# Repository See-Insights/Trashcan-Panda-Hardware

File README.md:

# Trashcan-Panda-Hardware
 Trashcan Panda project hardware files

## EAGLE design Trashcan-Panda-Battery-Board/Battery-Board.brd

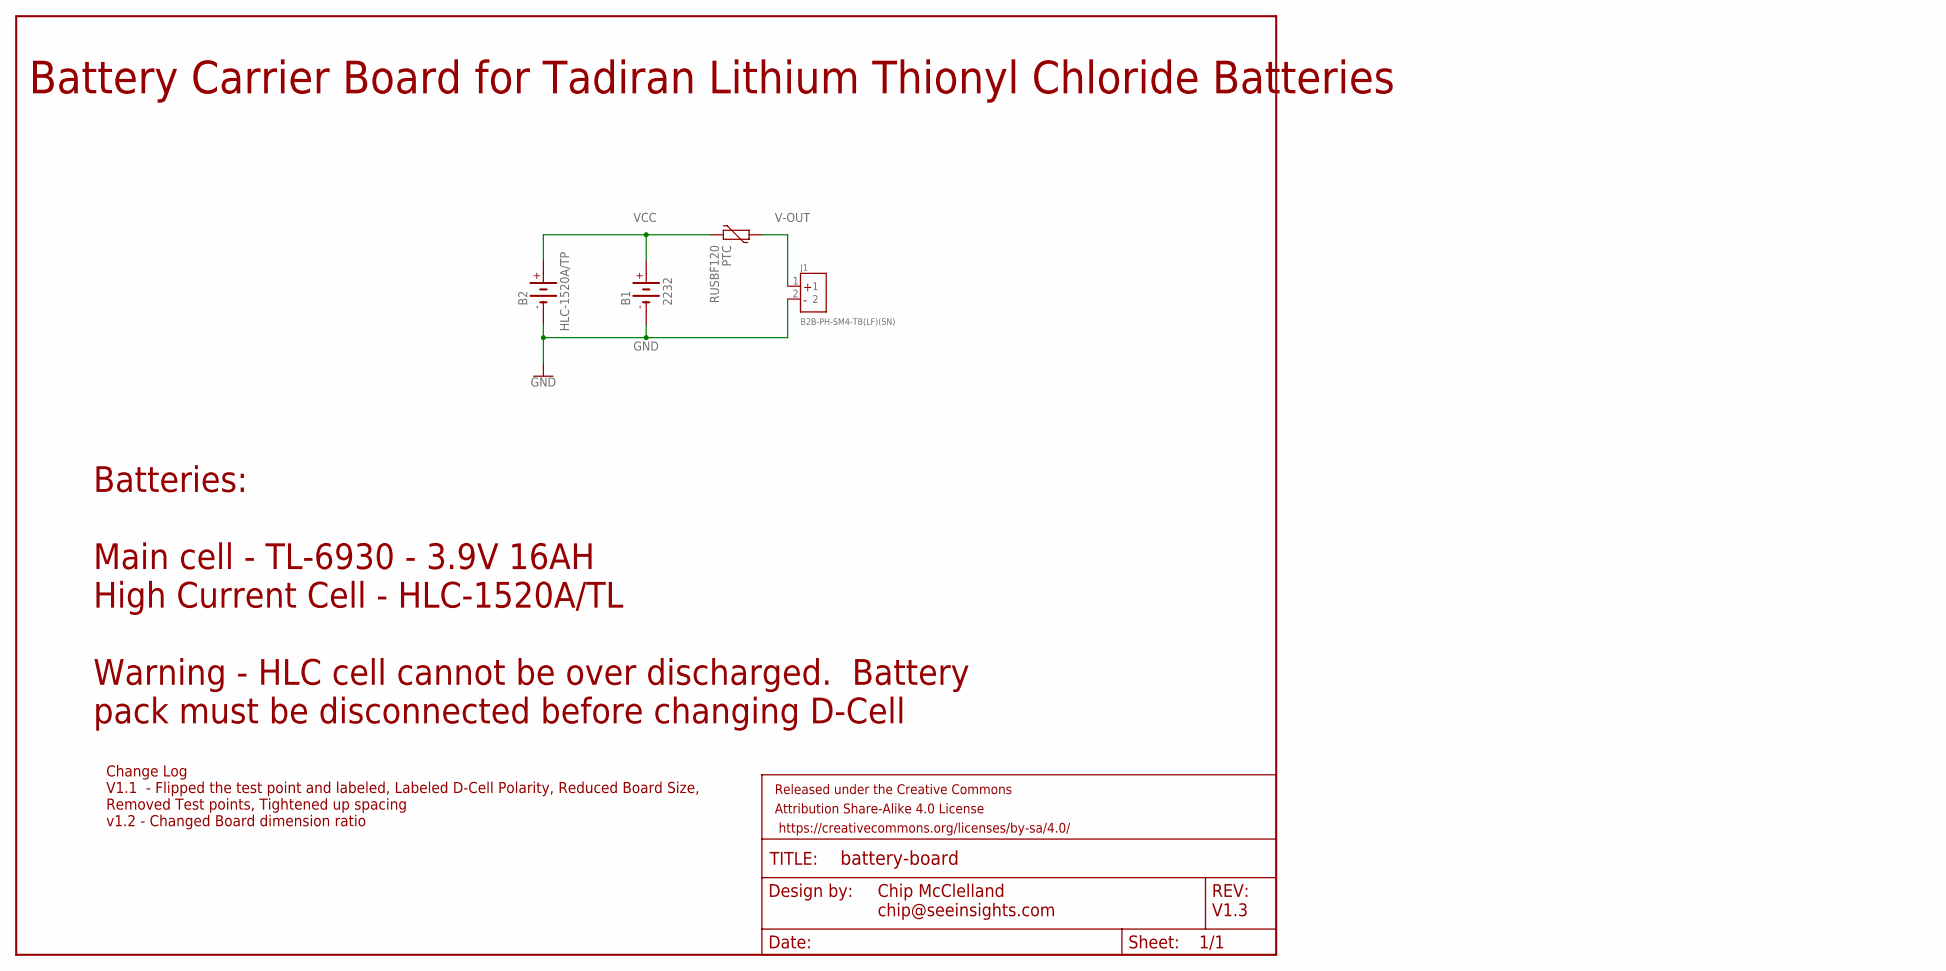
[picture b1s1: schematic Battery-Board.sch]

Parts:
B1: 2232
B2: HLC-1520A/TP
FRAME1: FRAME-LETTER; CREATIVE_COMMONS
J1: B2B-PH-SM4-TB(LF)(SN); JST_B2B-PH-SM4-TB(LF)(SN)
PTC: RUSBF120; PTC-RUSBF120

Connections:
GND: B1.-, B2.-, B2.-- (-), J1.2
V-OUT: J1.1, PTC.2
VCC: B1.+, B2.+, PTC.1

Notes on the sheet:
Battery Carrier Board for Tadiran Lithium Thionyl Chloride Batteries
Batteries: Main cell - TL-6930 - 3.9V 16AH High Current Cell - HLC-1520A/TL Warning - HLC cell cannot be over discharged. Battery pack must be disconnected before changing D-Cell
Chip McClelland chip@seeinsights.com
V1.3
Change Log V1.1 - Flipped the test point and labeled, Labeled D-Cell Polarity, Reduced Board Size, Removed Test points, Tightened up spacing v1.2 - Changed Board dimension ratio

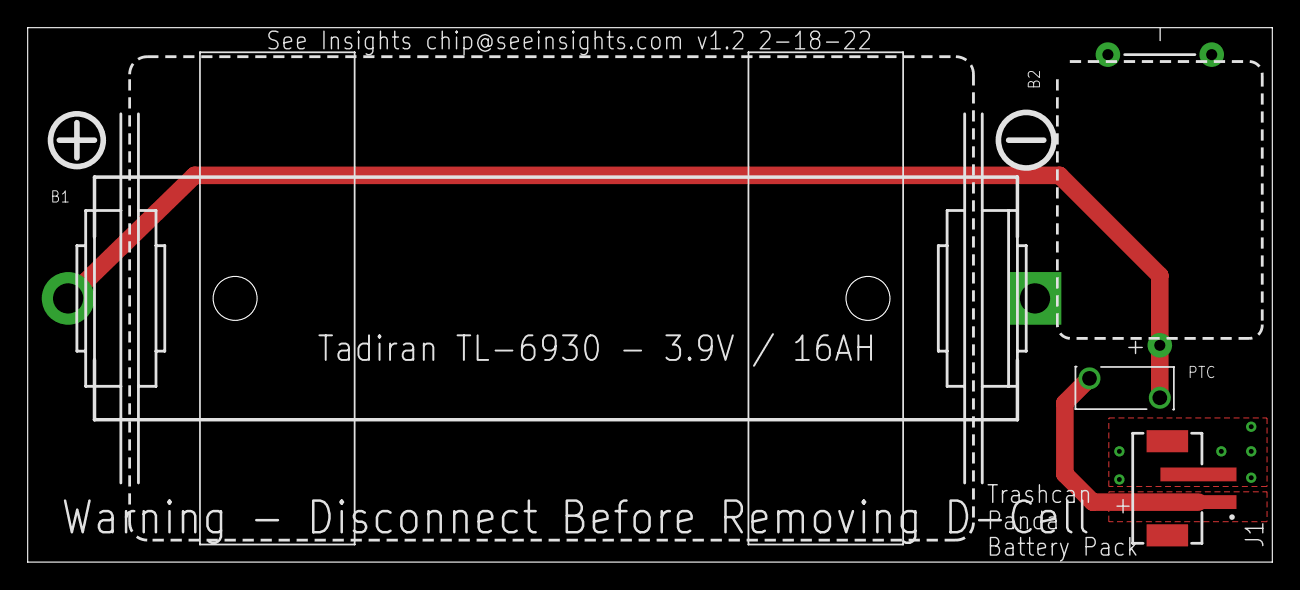
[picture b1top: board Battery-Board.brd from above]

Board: 2 copper layers, 89.9 x 38.6 mm, 5 parts (0 on the bottom side), 3 nets.

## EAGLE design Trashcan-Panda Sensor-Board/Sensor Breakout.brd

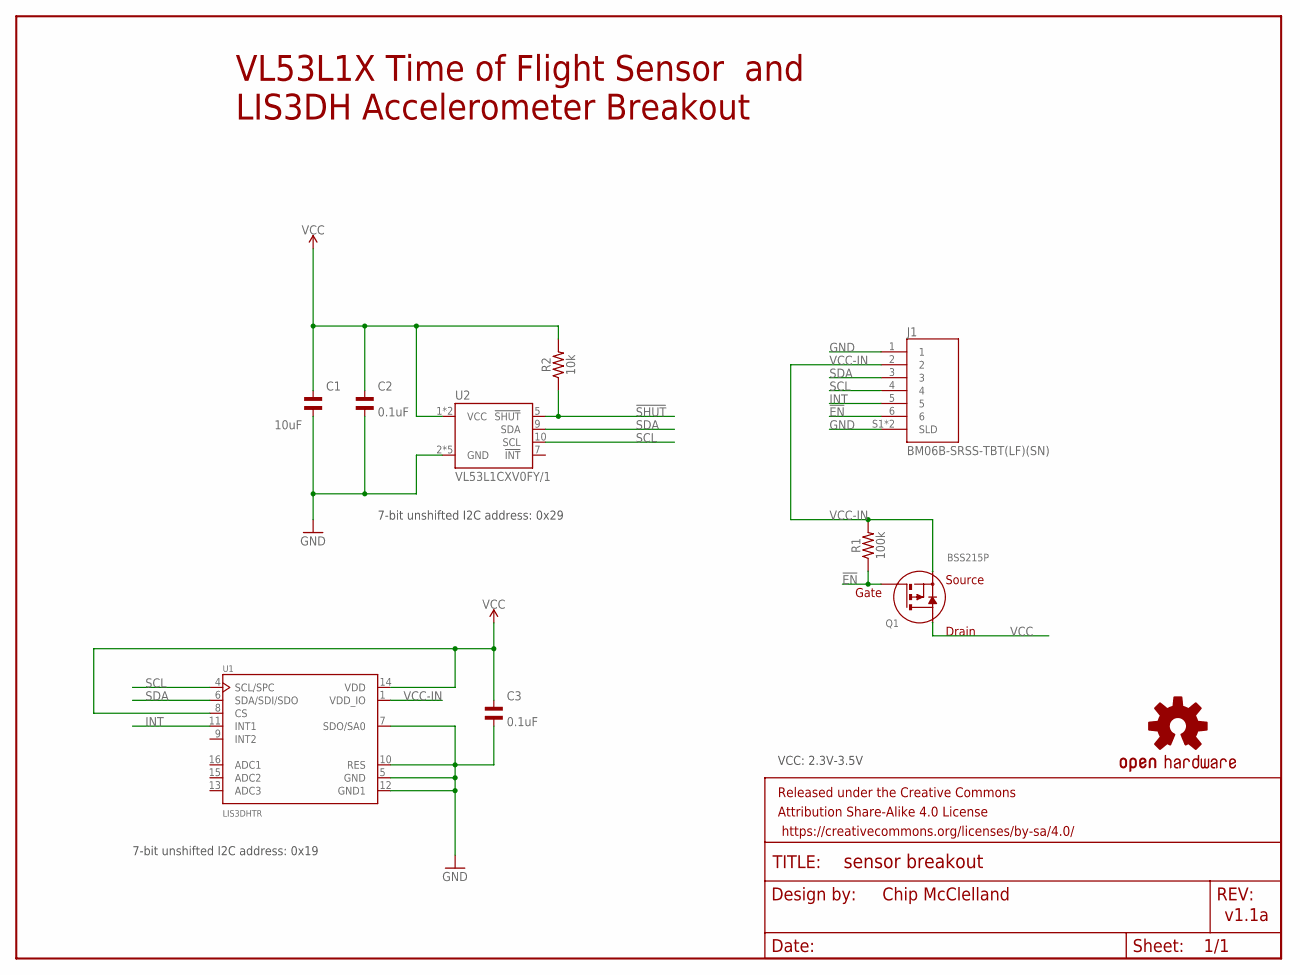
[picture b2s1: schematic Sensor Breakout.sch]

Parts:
C1: 10uF; C1206
C2, C3: 0.1uF; C0805
FRAME1: FRAME-LETTER; CREATIVE_COMMONS
J1: BM06B-SRSS-TBT(LF)(SN); JST_BM06B-SRSS-TB(LF)(SN)
LOGO1: OSHW-LOGOMINI; OSHW-LOGO-MINI
Q1: BSS215P; SOT-23_3L_ONS-M
R1: 100k; 0805; MPN MF-RES-0805-100K
R2: 10k; 0805
U1: LIS3DHTR; PQFN50P300X300X100-16N
U2: VL53L1CXV0FY/1; VL53L1X

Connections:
!EN: J1.6, Q1.1 (GATE), R1.1
!SHUT: R2.1, U2.5 (!SHUT)
GND: C1.P$2, C2.P$2, C3.P$2, J1.1, J1.S1 (SLD), J1.S2 (SLD), U1.5 (GND), U1.7 (SDO/SA0), U1.10 (RES), U1.12 (GND1), U2.2 (GND), U2.3 (GND), U2.4 (GND), U2.6 (GND), U2.12 (GND)
INT: J1.5, U1.11 (INT1)
SCL: J1.4, U1.4 (SCL/SPC), U2.10 (SCL)
SDA: J1.3, U1.6 (SDA/SDI/SDO), U2.9 (SDA)
VCC: C1.P$1, C2.P$1, C3.P$1, Q1.3 (DRAIN), R2.2, U1.8 (CS), U1.14 (VDD), U2.1 (VCC), U2.11 (VCC)
VCC-IN: J1.2, Q1.2 (SOURCE), R1.2, U1.1 (VDD_IO)

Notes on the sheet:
Chip McClelland
v1.1a
7-bit unshifted I2C address: 0x29
VCC: 2.3V-3.5V
VL53L1X Time of Flight Sensor and LIS3DH Accelerometer Breakout
7-bit unshifted I2C address: 0x19

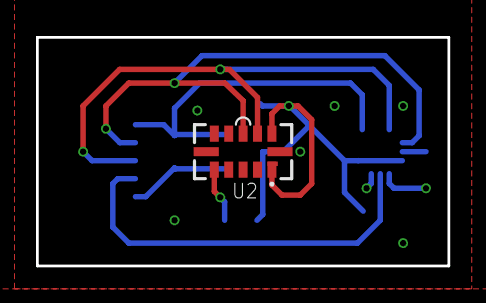
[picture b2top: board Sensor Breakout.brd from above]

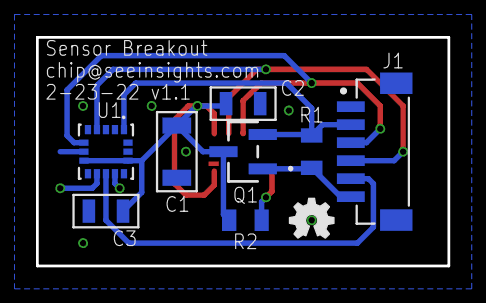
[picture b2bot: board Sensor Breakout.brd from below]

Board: 2 copper layers, 22.9 x 12.7 mm, 11 parts (9 on the bottom side), 8 nets.

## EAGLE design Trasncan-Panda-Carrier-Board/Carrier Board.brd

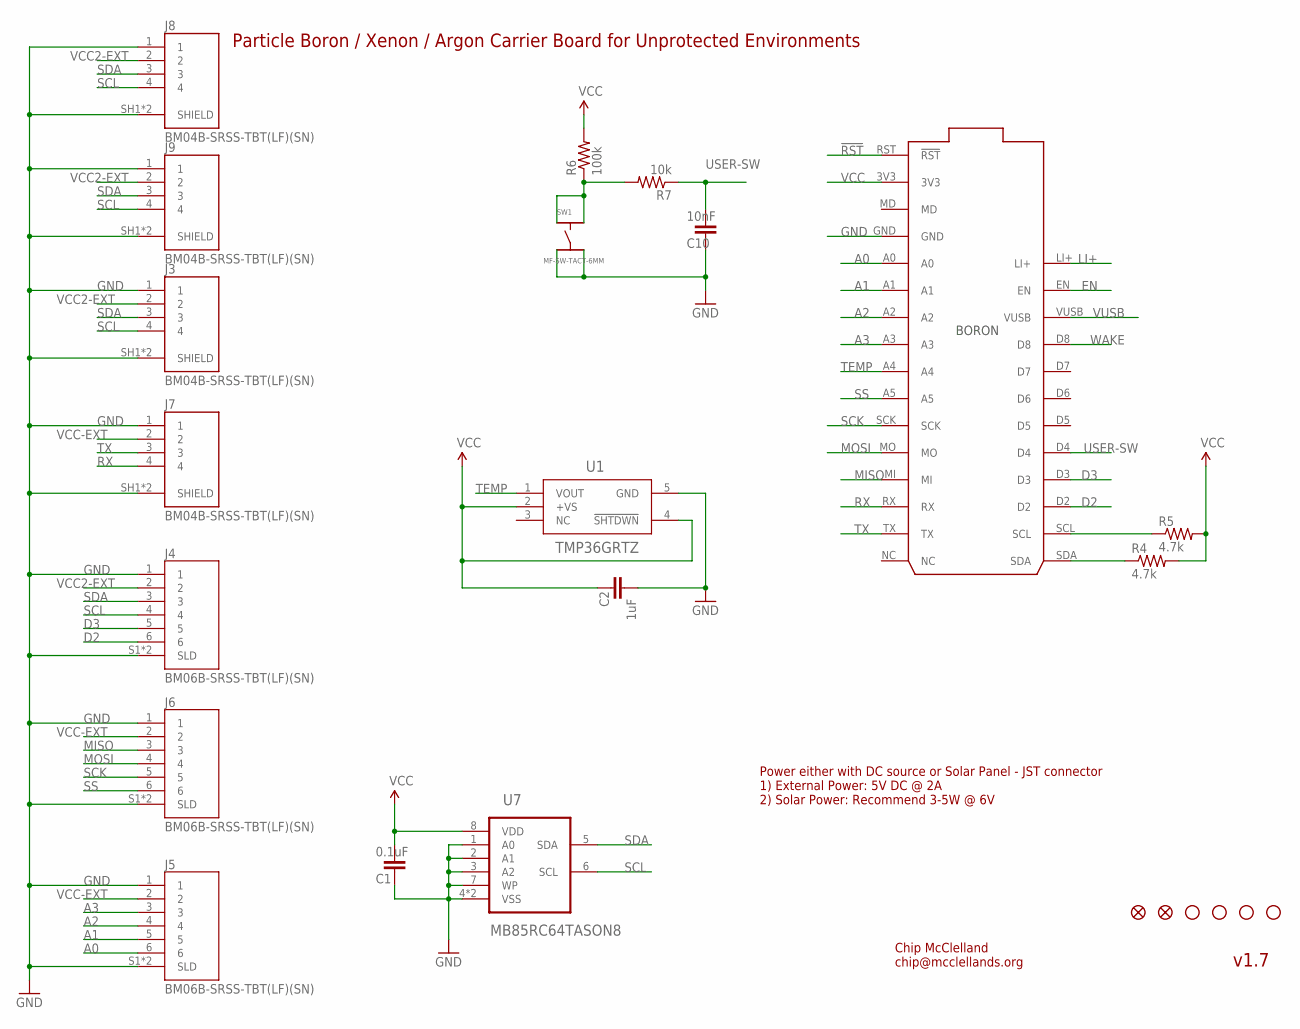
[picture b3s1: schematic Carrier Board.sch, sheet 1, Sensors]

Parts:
C1: 0.1uF; 0805@1; MPN MF-CAP-0805-0.1uF
C2: 1uF; 0805@1; MPN MF-CAP-0805-1uF
C10: 10nF; 0805@1; MPN 08051C103K4T2A
FD1, FD2: FIDUCIALUFIDUCIAL; FIDUCIAL-MICRO
J3, J7, J8, J9: BM04B-SRSS-TBT(LF)(SN); CONN_BM04B-SRSS-TBT(LF)(SN)
J4, J5, J6: BM06B-SRSS-TBT(LF)(SN); JST_BM06B-SRSS-TB(LF)(SN)
JP3, JP4, JP5, JP6: STAND-OFF
P1: Particle Boron / Xenon / Argon; PARTICLE-DEVICES_BORON
R4, R5: 4.7k; 0805; MPN MF-RES-0805-4.7K
R6: 100k; 0805; MPN MF-RES-0805-100K
R7: 10k; 0805; MPN MF-RES-0805-10K
SW1: MF-SW-TACT-6MM; TACT6MM
U1: TMP36GRTZ; RJ_5_ADI; MANUFACTURER_PART_NUMBER TMP36GRTZ-REEL7
U7: MB85RC64TASON8; SON50P200X300X75-9N

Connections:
!RST: P1.RST (!RST); also elsewhere on the board
A0: J5.6, P1.A0
A1: J5.5, P1.A1
A2: J5.4, P1.A2
A3: J5.3, P1.A3
D2: J4.6, P1.D2; also elsewhere on the board
D3: J4.5, P1.D3; also elsewhere on the board
EN: P1.EN; also elsewhere on the board
GND: C1.2, C2.2, C10.2, J3.1, J3.SH1 (SHIELD), J3.SH2 (SHIELD), J4.1, J4.S1 (SLD), J4.S2 (SLD), J5.1, J5.S1 (SLD), J5.S2 (SLD), J6.1, J6.S1 (SLD), J6.S2 (SLD), J7.1, J7.SH1 (SHIELD), J7.SH2 (SHIELD), J8.1, J8.SH1 (SHIELD), J8.SH2 (SHIELD), J9.1, J9.SH1 (SHIELD), J9.SH2 (SHIELD), P1.GND, SW1.P$3, SW1.P$4, U1.5 (GND), U7.1 (A0), U7.2 (A1), U7.3 (A2), U7.4 (VSS), U7.7 (WP), U7.9 (VSS); also elsewhere on the board
LI+: P1.LI+; also elsewhere on the board
MISO: J6.3, P1.MI
MOSI: J6.4, P1.MO
unnamed: R6.1, R7.2, SW1.P$1, SW1.P$2
RX: J7.4, P1.RX
SCK: J6.5, P1.SCK
SCL: J3.4, J4.4, J8.4, J9.4, P1.SCL, R5.1, U7.6 (SCL); also elsewhere on the board
SDA: J3.3, J4.3, J8.3, J9.3, P1.SDA, R4.1, U7.5 (SDA); also elsewhere on the board
SS: J6.6, P1.A5
TEMP: P1.A4, U1.1 (VOUT)
TX: J7.3, P1.TX
USER-SW: C10.1, P1.D4, R7.1
VCC: C1.1, C2.1, P1.3V3, R4.2, R5.2, R6.2, U1.2 (+VS), U1.4 (!SHTDWN), U7.8 (VDD); also elsewhere on the board
VCC2-EXT: J3.2, J4.2, J8.2, J9.2; also elsewhere on the board
VCC-EXT: J5.2, J6.2, J7.2; also elsewhere on the board
VUSB: P1.VUSB; also elsewhere on the board
WAKE: P1.D8; also elsewhere on the board

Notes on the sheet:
Chip McClelland chip@mcclellands.org
v1.7
Power either with DC source or Solar Panel - JST connector 1) External Power: 5V DC @ 2A 2) Solar Power: Recommend 3-5W @ 6V
Particle Boron / Xenon / Argon Carrier Board for Unprotected Environments

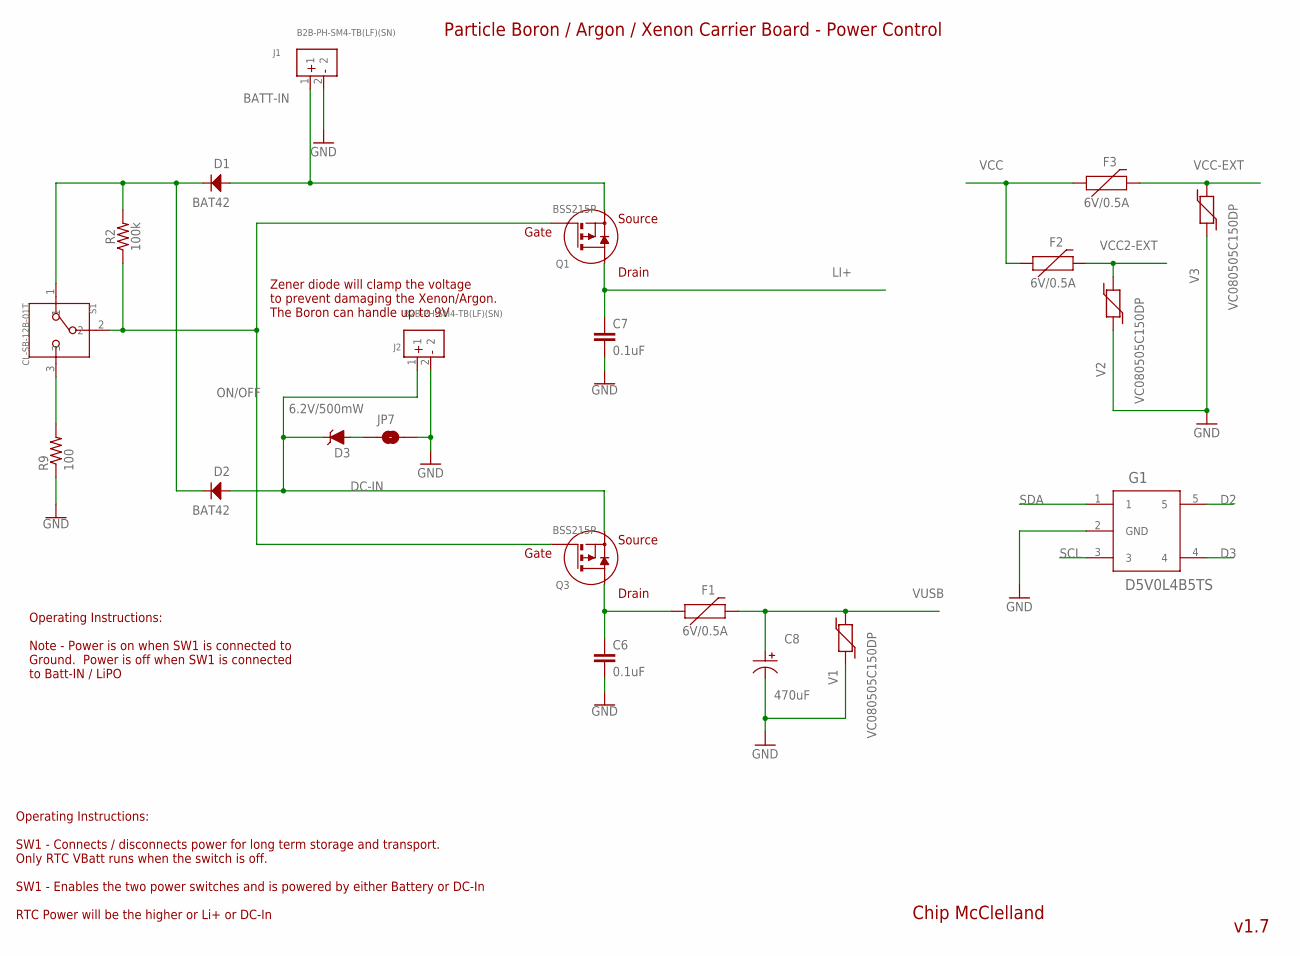
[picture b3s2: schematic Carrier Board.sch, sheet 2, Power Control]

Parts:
C6, C7: 0.1uF; 0805@1; MPN MF-CAP-0805-0.1uF
C8: 470uF; CP10MM; MPN MF-CAP-10MM-470uF
D1, D2: BAT42; SOD-123
D3: 6.2V/500mW; PANASONIC_SMINI2-F5-B; MPN TDZ6V2J,115
F1: 6V/0.5A; 1206; MPN 046801.5NR
F2, F3: 6V/0.5A; 1206; MPN 0466.500NR
G1: D5V0L4B5TS; SOT-23-5; MPN D5V0L4B5TS-7
J1, J2: B2B-PH-SM4-TB(LF)(SN); JST_B2B-PH-SM4-TB(LF)(SN)
JP7: JUMPER-SMT_2_NO_SILK; SMT-JUMPER_2_NO_SILK
Q1, Q3: BSS215P; SOT-23_3L_ONS-M
R2: 100k; 0805
R9: 100; 0805; MPN MF-RES-0805-100
S1: CL-SB-12B-01T; CL-SB-12B
V1, V2, V3: VC080505C150DP; 0805; MPN VC080505C150DP

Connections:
BATT-IN: D1.ANODE, J1.1, Q1.2 (SOURCE); also elsewhere on the board
D2: G1.5; also elsewhere on the board
D3: G1.4; also elsewhere on the board
DC-IN: D2.ANODE, D3.C, J2.1, Q3.2 (SOURCE)
GND: C6.2, C7.2, C8.P$2, G1.2 (GND), J1.2, J2.2, JP7.1, R9.1, V1.1, V2.1, V3.1; also elsewhere on the board
LI+: C7.1, Q1.3 (DRAIN); also elsewhere on the board
unnamed: D3.A, JP7.2
unnamed: C6.1, F1.1, Q3.3 (DRAIN)
unnamed: D1.CATHODE, D2.CATHODE, R2.2, S1.1
unnamed: R9.2, S1.3
ON/OFF: Q1.1 (GATE), Q3.1 (GATE), R2.1, S1.2
SCL: G1.3; also elsewhere on the board
SDA: G1.1; also elsewhere on the board
VCC: F2.1, F3.1; also elsewhere on the board
VCC2-EXT: F2.2, V2.2; also elsewhere on the board
VCC-EXT: F3.2, V3.2; also elsewhere on the board
VUSB: C8.P$1, F1.2, V1.2; also elsewhere on the board

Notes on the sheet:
Particle Boron / Argon / Xenon Carrier Board - Power Control
Chip McClelland
v1.7
Operating Instructions: SW1 - Connects / disconnects power for long term storage and transport. Only RTC VBatt runs when the switch is off. SW1 - Enables the two power switches and is powered by either Battery or DC-In RTC Power will be the higher or Li+ or DC-In
Zener diode will clamp the voltage to prevent damaging the Xenon/Argon. The Boron can handle up to 9V
Operating Instructions: Note - Power is on when SW1 is connected to Ground. Power is off when SW1 is connected to Batt-IN / LiPO

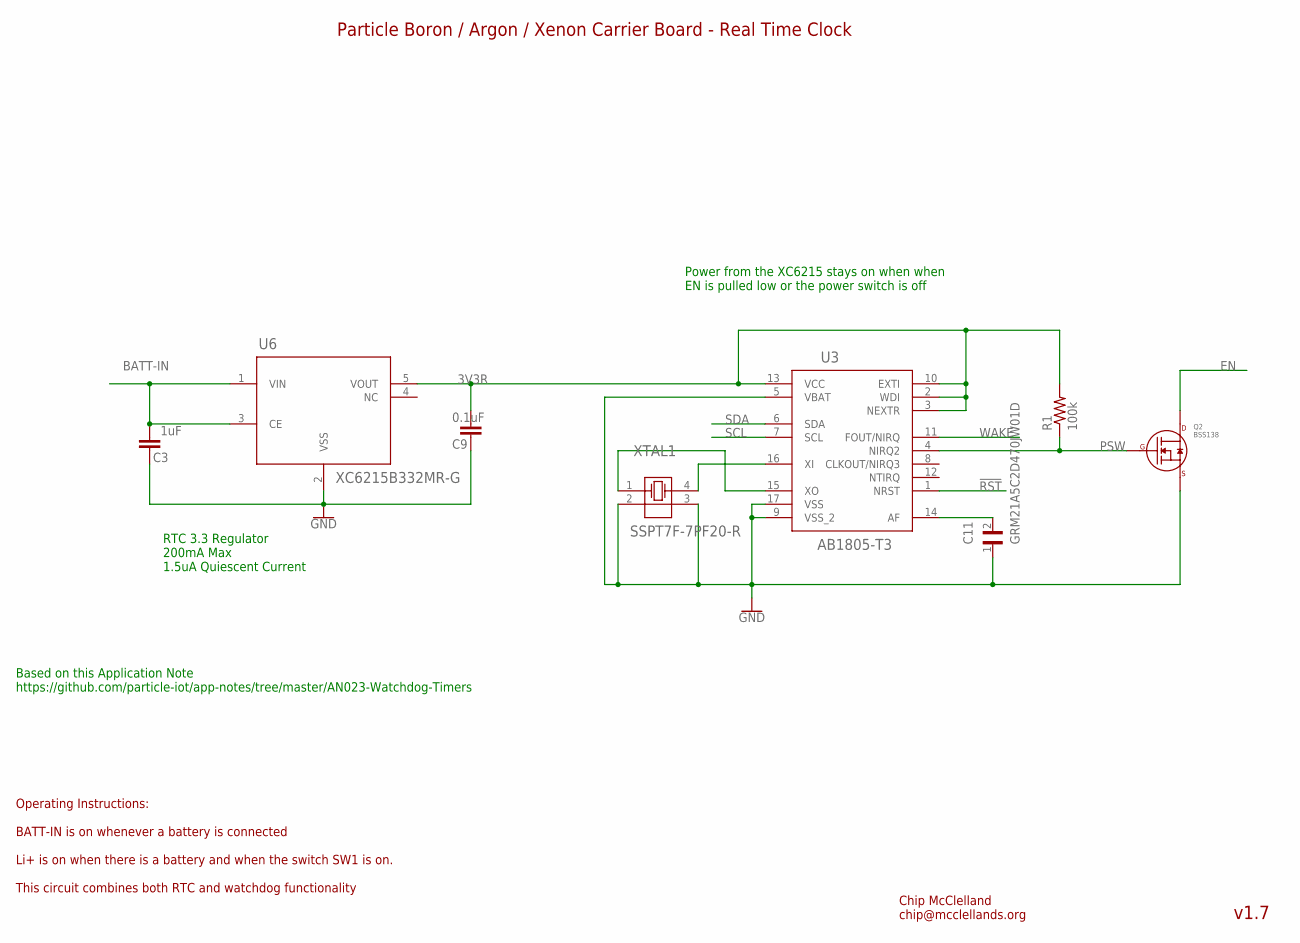
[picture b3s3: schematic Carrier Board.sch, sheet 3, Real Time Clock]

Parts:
C3: 1uF; 0805@1; MPN MF-CAP-0805-1uF
C9: 0.1uF; 0805@1; MPN MF-CAP-0805-0.1uF
C11: GRM21A5C2D470JW01D; CAPC2012X100N
Q2: BSS138; SOT-23_3L_ONS
R1: 100k; 0805; MPN MF-RES-0805-100K
U3: AB1805-T3; QFN_16_ABR
U6: XC6215B332MR-G; SOT-25_TOR
XTAL1: SSPT7F-7PF20-R; SSP-T7-F_EPS

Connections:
3V3R: C9.1, R1.2, U3.2 (WDI), U3.3 (NEXTR), U3.10 (EXTI), U3.13 (VCC), U6.5 (VOUT)
!RST: U3.1 (NRST); also elsewhere on the board
BATT-IN: C3.2, U6.1 (VIN), U6.3 (CE); also elsewhere on the board
EN: Q2.3 (DRAIN); also elsewhere on the board
GND: C3.1, C9.2, C11.1, Q2.2 (SOURCE), U3.5 (VBAT), U3.9 (VSS_2), U3.17 (VSS), U6.2 (VSS), XTAL1.2, XTAL1.3; also elsewhere on the board
unnamed: U3.15 (XO), XTAL1.1
unnamed: U3.16 (XI), XTAL1.4
unnamed: C11.2, U3.14 (AF)
PSW: Q2.1 (GATE), R1.1, U3.4 (NIRQ2)
SCL: U3.7 (SCL); also elsewhere on the board
SDA: U3.6 (SDA); also elsewhere on the board
WAKE: U3.11 (FOUT/NIRQ); also elsewhere on the board

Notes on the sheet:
Operating Instructions: BATT-IN is on whenever a battery is connected Li+ is on when there is a battery and when the switch SW1 is on. This circuit combines both RTC and watchdog functionality
Particle Boron / Argon / Xenon Carrier Board - Real Time Clock
Chip McClelland chip@mcclellands.org
v1.7
RTC 3.3 Regulator 200mA Max 1.5uA Quiescent Current
Power from the XC6215 stays on when when EN is pulled low or the power switch is off
Based on this Application Note https://github.com/particle-iot/app-notes/tree/master/AN023-Watchdog-Timers

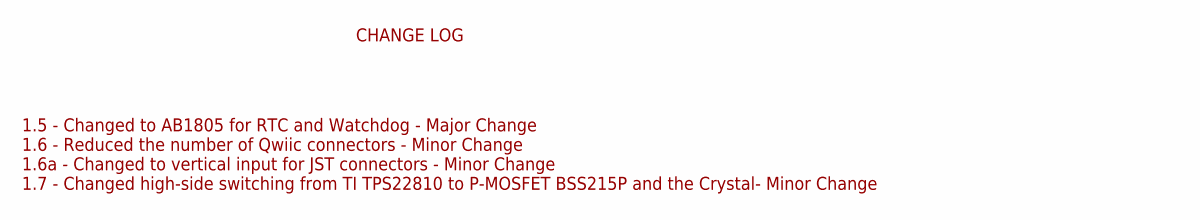
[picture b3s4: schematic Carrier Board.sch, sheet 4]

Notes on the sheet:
CHANGE LOG
1.5 - Changed to AB1805 for RTC and Watchdog - Major Change 1.6 - Reduced the number of Qwiic connectors - Minor Change 1.6a - Changed to vertical input for JST connectors - Minor Change 1.7 - Changed high-side switching from TI TPS22810 to P-MOSFET BSS215P and the Crystal- Minor Change

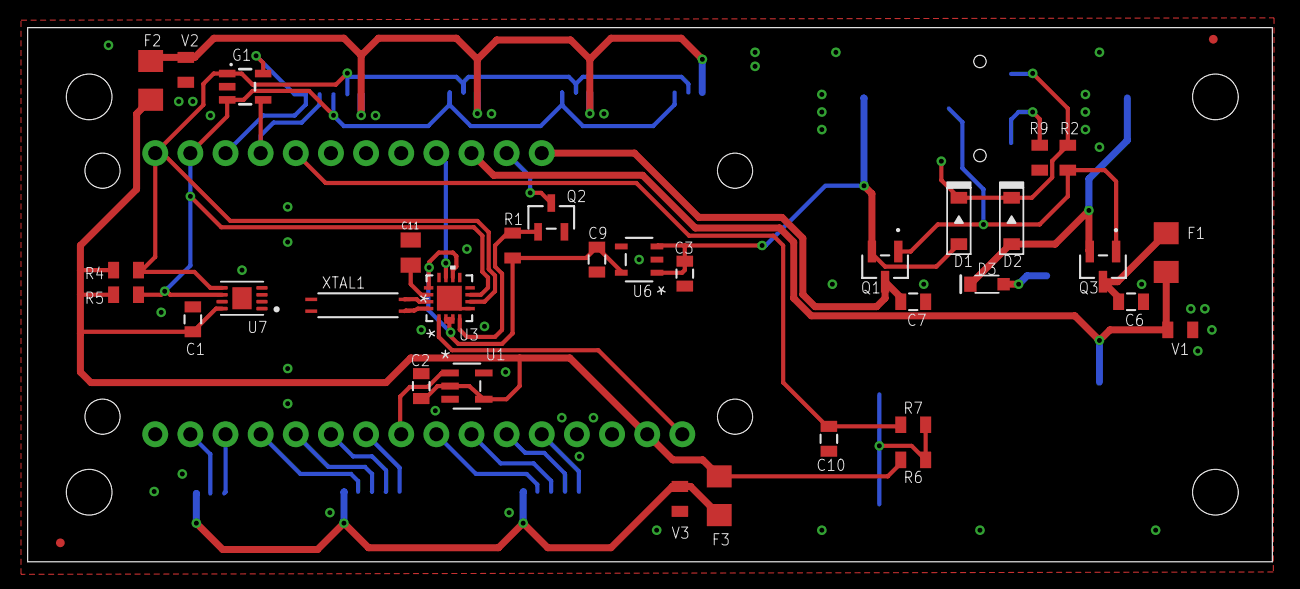
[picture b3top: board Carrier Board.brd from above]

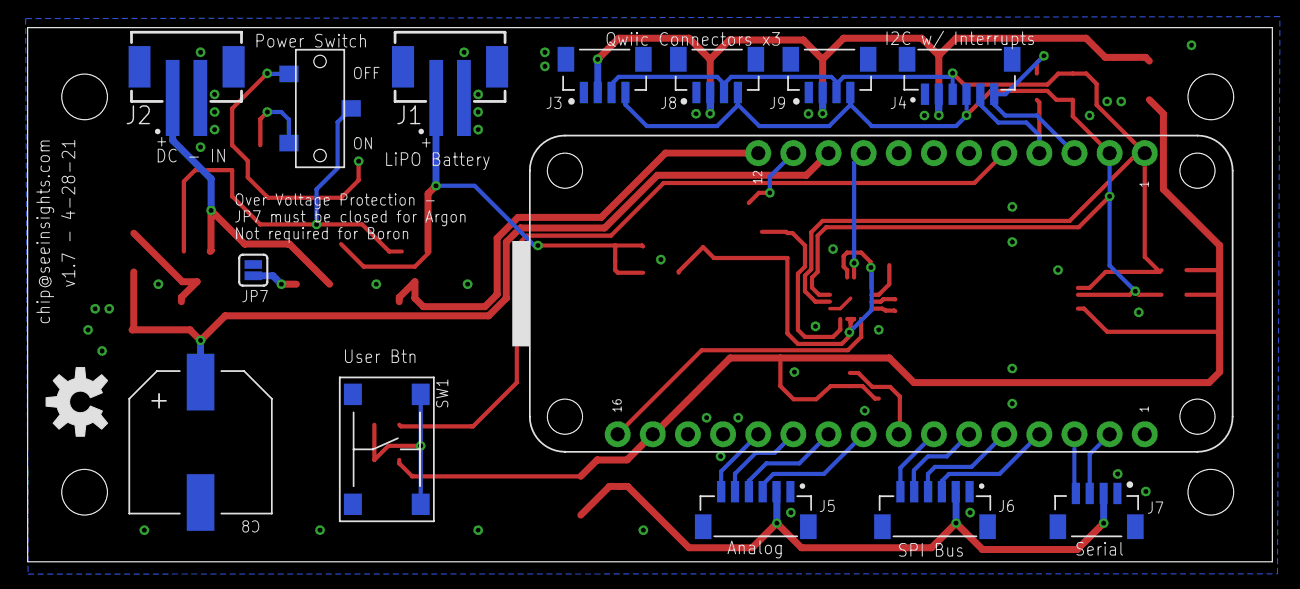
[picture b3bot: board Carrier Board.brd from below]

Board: 2 copper layers, 90.0 x 38.6 mm, 54 parts (15 on the bottom side), 38 nets.

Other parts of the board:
U$2: OSHW-LOGO-M

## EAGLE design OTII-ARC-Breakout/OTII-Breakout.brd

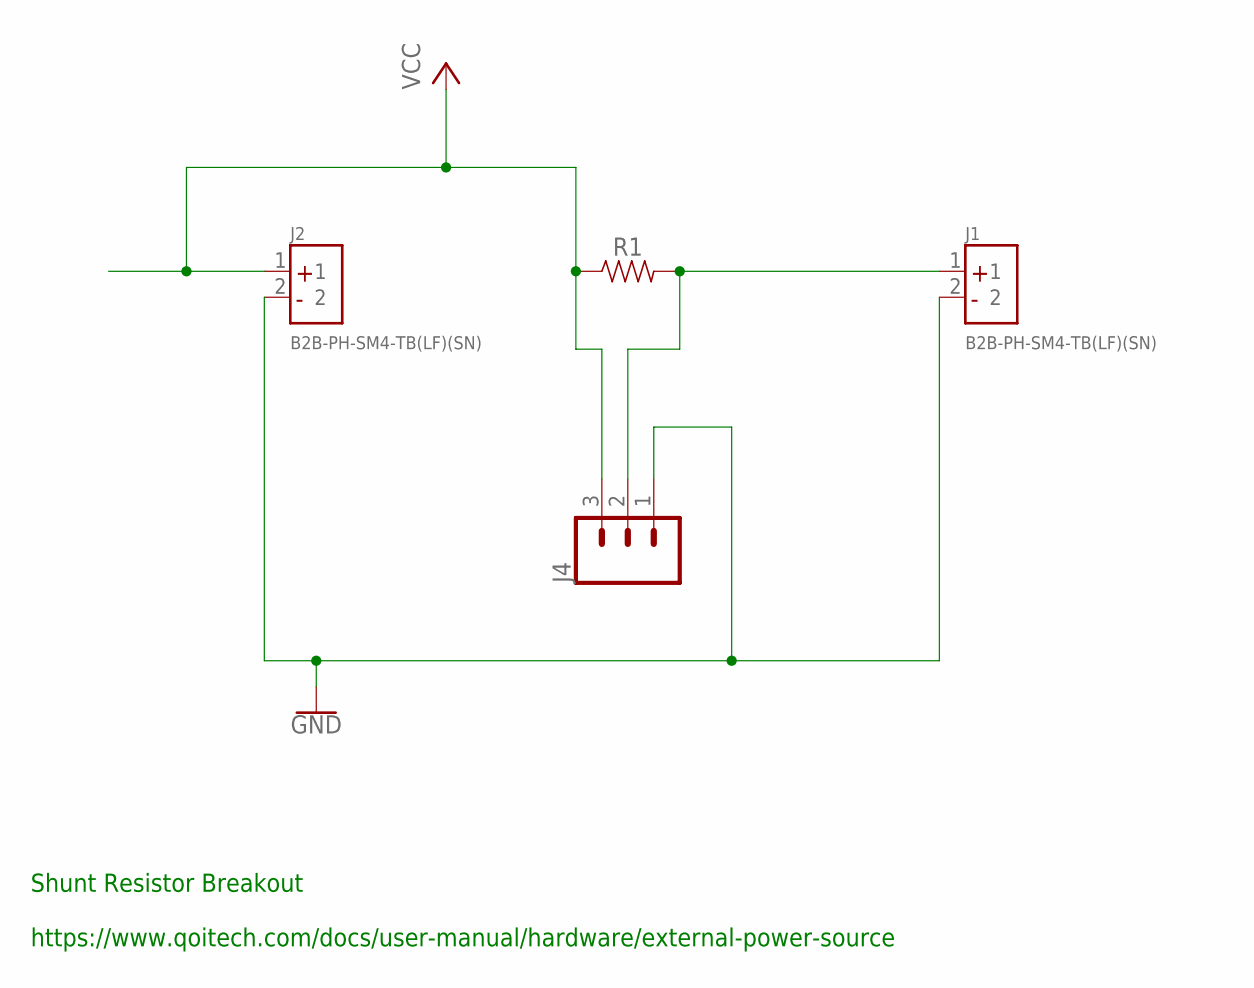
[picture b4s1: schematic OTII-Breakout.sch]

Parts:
J1, J2: B2B-PH-SM4-TB(LF)(SN); JST_B2B-PH-SM4-TB(LF)(SN)
J4: CONN_03; 1X03
R1: 0805

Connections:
GND: J1.2, J2.2, J4.1
unnamed: J1.1, J4.2, R1.2
VCC: J2.1, J4.3, R1.1

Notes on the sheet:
Shunt Resistor Breakout https://www.qoitech.com/docs/user-manual/hardware/external-power-source

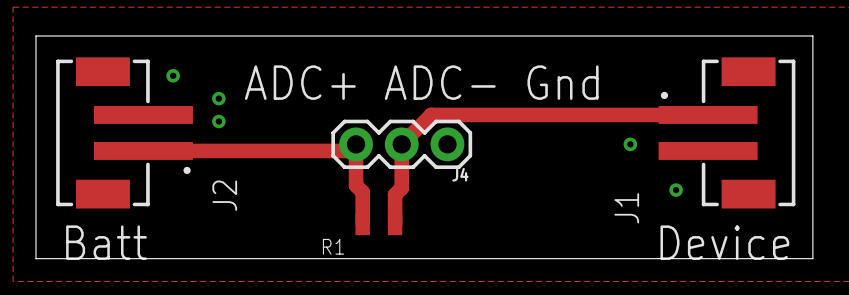
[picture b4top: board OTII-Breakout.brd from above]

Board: 2 copper layers, 43.2 x 12.4 mm, 4 parts (0 on the bottom side), 3 nets.

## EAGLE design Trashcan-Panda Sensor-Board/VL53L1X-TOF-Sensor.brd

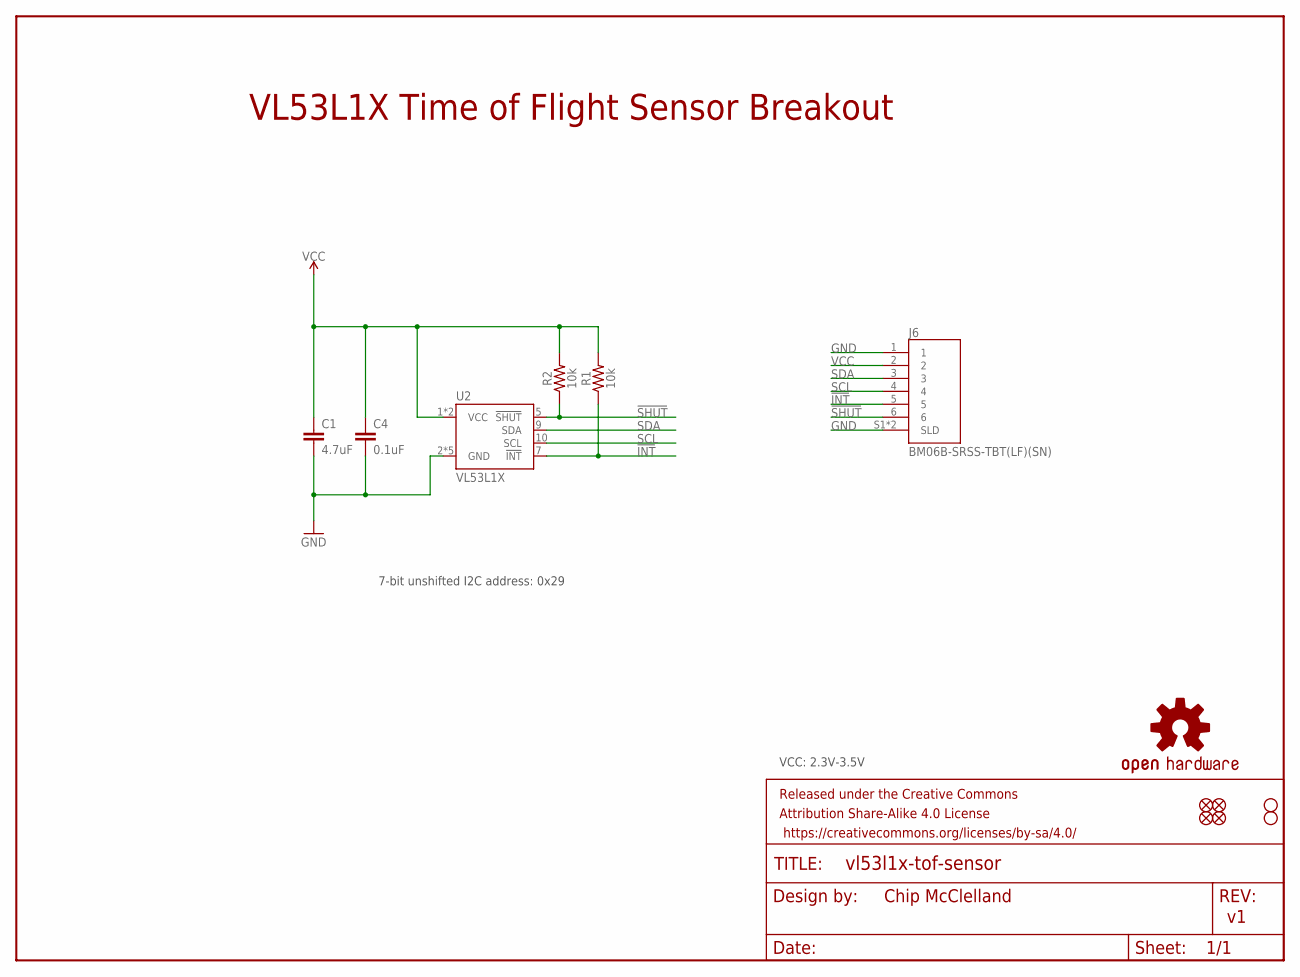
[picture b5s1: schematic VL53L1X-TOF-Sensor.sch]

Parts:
C1: 4.7uF; 0603
C4: 0.1uF; 0603
FRAME1: FRAME-LETTER; CREATIVE_COMMONS
J6: BM06B-SRSS-TBT(LF)(SN); JST_BM06B-SRSS-TB(LF)(SN)
JP1, JP2, JP5, JP6: FIDUCIALUFIDUCIAL; MICRO-FIDUCIAL
JP3, JP4: STAND-OFF
LOGO1: OSHW-LOGOMINI; OSHW-LOGO-MINI
R1, R2: 10k; 0603
U2: VL53L1X

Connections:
!INT: J6.5, R1.1, U2.7 (!INT)
!SHUT: J6.6, R2.1, U2.5 (!SHUT)
GND: C1.2, C4.2, J6.1, J6.S1 (SLD), J6.S2 (SLD), U2.2 (GND), U2.3 (GND), U2.4 (GND), U2.6 (GND), U2.12 (GND)
SCL: J6.4, U2.10 (SCL)
SDA: J6.3, U2.9 (SDA)
VCC: C1.1, C4.1, J6.2, R1.2, R2.2, U2.1 (VCC), U2.11 (VCC)

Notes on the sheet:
Chip McClelland
7-bit unshifted I2C address: 0x29
VCC: 2.3V-3.5V
VL53L1X Time of Flight Sensor Breakout

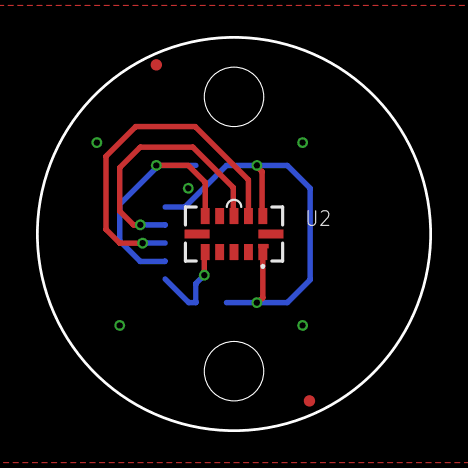
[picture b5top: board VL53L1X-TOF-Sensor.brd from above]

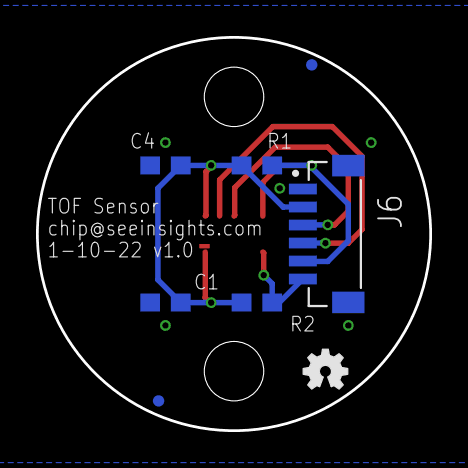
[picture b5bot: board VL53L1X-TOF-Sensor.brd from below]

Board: 2 copper layers, 21.8 x 21.8 mm, 14 parts (8 on the bottom side), 6 nets.

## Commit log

2022-02-19 Updates for breakout board
2022-02-23 Rectangular Sensor Board
2022-03-14 Updated battery board to v1.1
2022-03-17 Updated - Grounded address pin
2022-03-17 Changed Battery Board Profile
2022-03-21 Updated for Macrofab house parts
2022-03-30 Adding datasheets
2022-03-30 Added pictures as case evolves
2022-04-09 Added PTC
2022-04-09 Added PTC datasheet
2022-04-23 More datasheets
2022-04-29 Adding assembled device photos

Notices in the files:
parts and their libraries:
SparkFun-Connectors: Licensing: Creative Commons ShareAlike 4.0 International - https://creativecommons.org/licenses/by-sa/4.0
SparkFun-Aesthetics: Released under the Creative Commons Attribution Share-Alike 4.0 License
SparkFun-Aesthetics: https://creativecommons.org/licenses/by-sa/4.0
